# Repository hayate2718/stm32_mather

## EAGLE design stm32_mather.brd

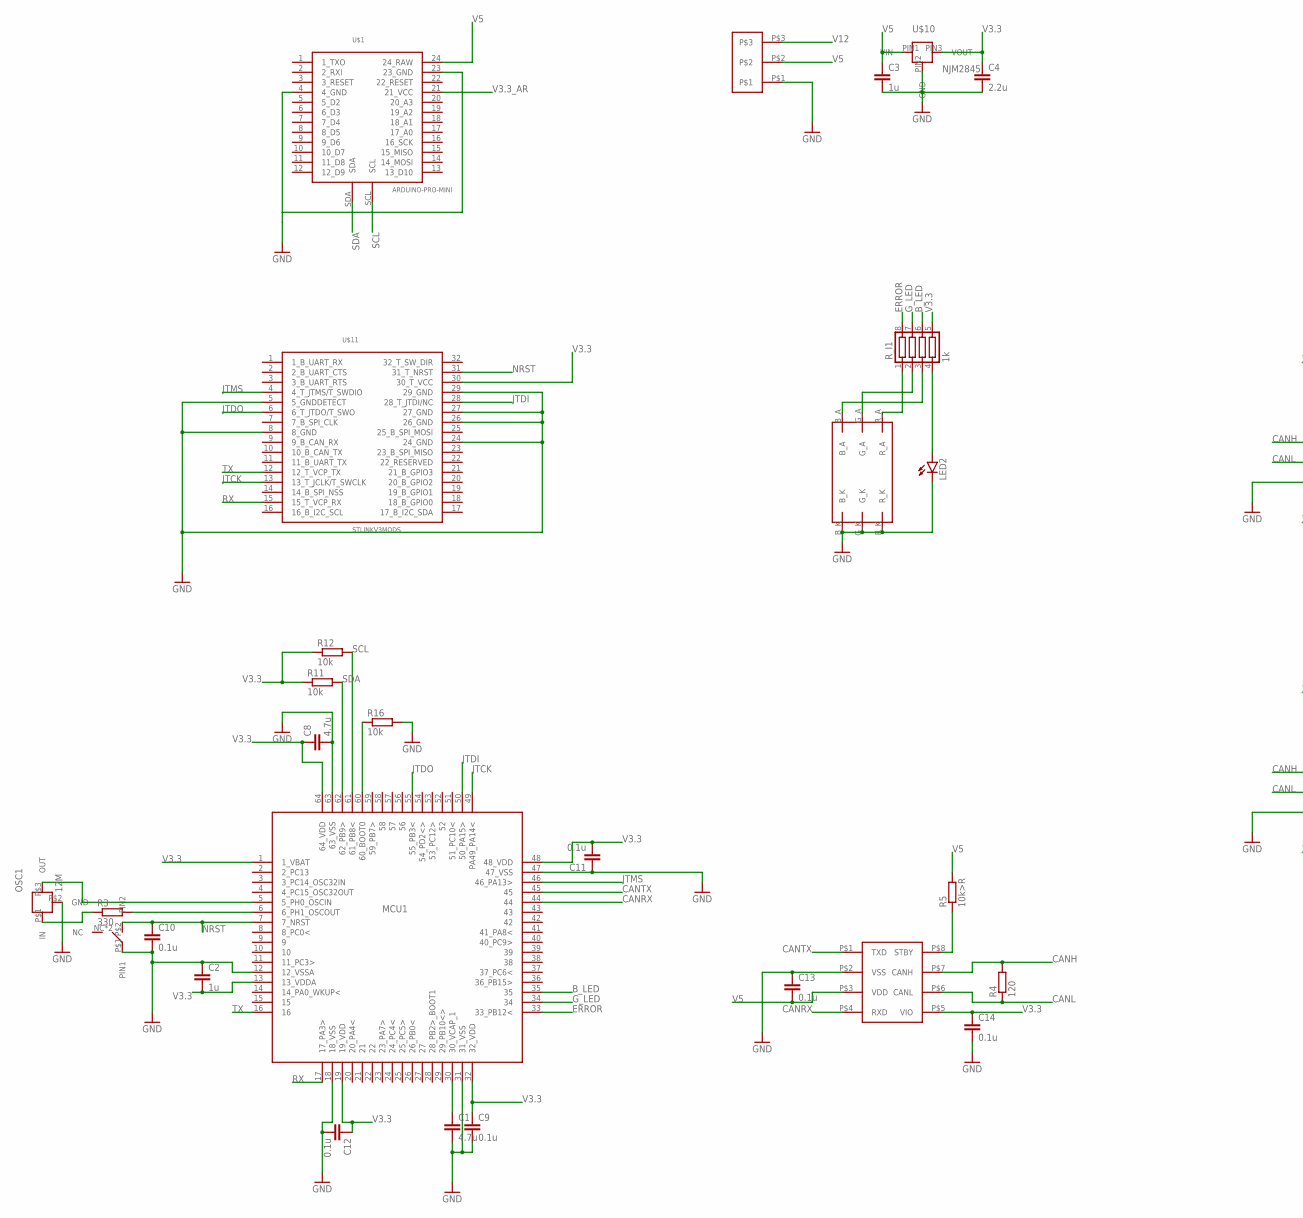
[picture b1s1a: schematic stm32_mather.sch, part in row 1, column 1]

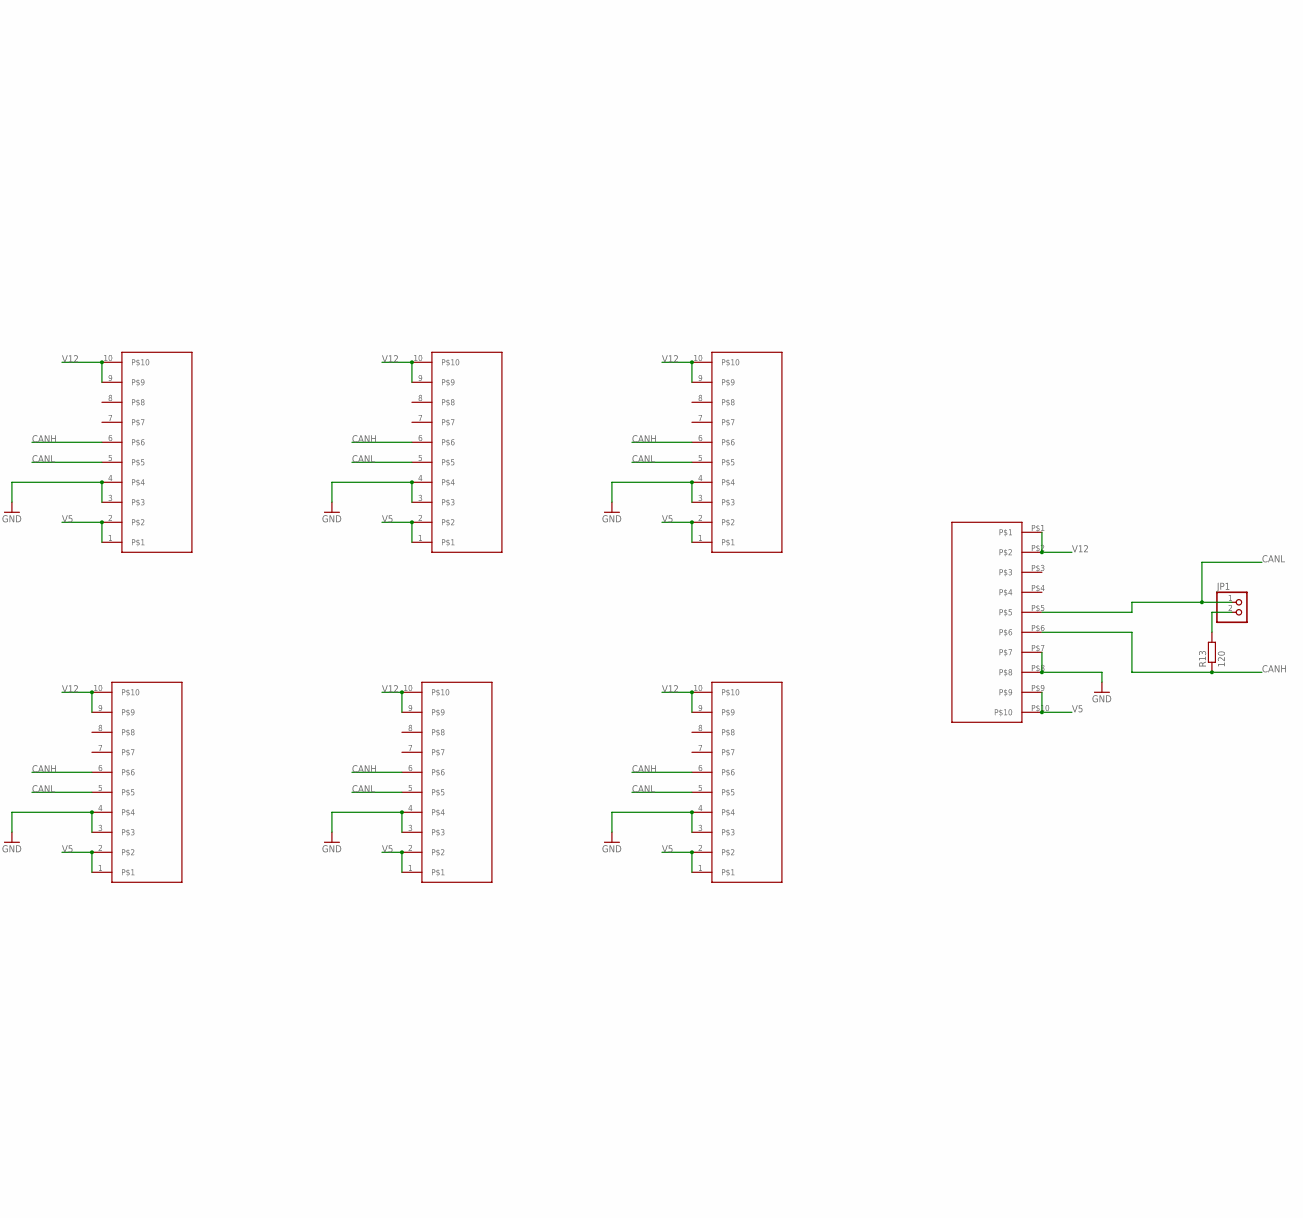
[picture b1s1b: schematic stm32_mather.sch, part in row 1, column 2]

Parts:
C1, C8: 4.7u; C1608
C2, C3: 1u; C1608
C4: 2.2u; C1608
C9, C10, C11, C12, C13, C14: 0.1u; C1608
JP1: PINHD-1X2; 1X02
LED2: 1608LED; 1608
MCU1: STM32F446; LQFP64-2
OSC1: 12M; CSTNE#
R3: 330; 1608
R4, R13: 120; 1608
R5: 10k>R; 1608
R11, R12, R16: 10k; 1608
R_I1: 1k; 0603X4RESISTOR
U$1: ARDUINO-PRO-MINI; ARDUINO_PRO_MINI
U$2, U$3, U$4, U$5, U$6, U$7: BOX10PBOX10PIN-MESU; BOX10P-MESU
U$8: BOX10PBOX10P-L; BOX10P-L
U$9: YUROBLOCK3
U$10: NJM2845; TO252
U$11: STLINKV3MODS
U$12: TAKUTOSUITTI2
U$13: MCP2562MCP2561-SN; SOIC8
U$15: RGB_LED

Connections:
B_LED: MCU1.35, R_I1.6
CANH: R4.2, R13.1, U$2.6, U$3.6, U$4.6, U$5.6, U$6.6, U$7.6, U$8.P$6, U$13.P$7 (CANH)
CANL: JP1.1, R4.1, U$2.5, U$3.5, U$4.5, U$5.5, U$6.5, U$7.5, U$8.P$5, U$13.P$6 (CANL)
CANRX: MCU1.44, U$13.P$4 (RXD)
CANTX: MCU1.45, U$13.P$1 (TXD)
ERROR: MCU1.33 (33_PB12<), R_I1.8
GND: C1.2, C2.1, C3.2, C4.2, C8.2, C9.2, C10.2, C11.1, C12.2, C13.1, C14.2, LED2.K, MCU1.12 (12_VSSA), MCU1.18 (18_VSS), MCU1.31 (31_VSS), MCU1.47 (47_VSS), MCU1.63 (63_VSS), OSC1.P$2 (GND), R16.2, U$1.4 (4_GND), U$1.23 (23_GND), U$2.3, U$2.4, U$3.3, U$3.4, U$4.3, U$4.4, U$5.3, U$5.4, U$6.3, U$6.4, U$7.3, U$7.4, U$8.P$7, U$8.P$8, U$9.P$1, U$10.PIN2 (GND), U$11.5 (5_GNDDETECT), U$11.8 (8_GND), U$11.24 (24_GND), U$11.26 (26_GND), U$11.27 (27_GND), U$11.29 (29_GND), U$12.P$1 (PIN1), U$13.P$2 (VSS), U$15.B_K, U$15.G_K, U$15.R_K
G_LED: MCU1.34, R_I1.7
JTCK: MCU1.49 (PA49_PA14<), U$11.13 (13_T_JCLK/T_SWCLK)
JTDI: MCU1.50 (50_PA15>), U$11.28 (28_T_JTDI/NC)
JTDO: MCU1.55 (55_PB3<), U$11.6 (6_T_JTDO/T_SWO)
JTMS: MCU1.46 (46_PA13>), U$11.4 (4_T_JTMS/T_SWDIO)
unnamed: C1.1, MCU1.30 (30_VCAP_1)
unnamed: OSC1.P$1 (IN), R3.1
unnamed: R_I1.1, U$15.R_A
unnamed: MCU1.5 (5_PH0_OSCIN), OSC1.P$3 (OUT)
unnamed: MCU1.6 (6_PH1_OSCOUT), R3.2
unnamed: R5.1, U$13.P$8 (STBY)
unnamed: JP1.2, R13.2
unnamed: R_I1.2, U$15.G_A
unnamed: R_I1.3, U$15.B_A
unnamed: LED2.A, R_I1.4
unnamed: MCU1.60 (60_BOOT0), R16.1
NRST: C10.1, MCU1.7 (7_NRST), U$11.31 (31_T_NRST), U$12.P$2 (PIN2)
RX: MCU1.17 (17_PA3>), U$11.15 (15_T_VCP_RX)
SCL: MCU1.61 (61_PB8<), R12.2, U$1.SCL
SDA: MCU1.62 (62_PB9>), R11.2, U$1.SDA
TX: MCU1.16, U$11.12 (12_T_VCP_TX)
V3.3: C2.2, C4.1, C8.1, C9.1, C11.2, C12.1, C14.1, MCU1.1 (1_VBAT), MCU1.13 (13_VDDA), MCU1.19 (19_VDD), MCU1.32 (32_VDD), MCU1.48 (48_VDD), MCU1.64 (64_VDD), R11.1, R12.1, R_I1.5, U$10.PIN3 (VOUT), U$11.30 (30_T_VCC), U$13.P$5 (VIO)
V3.3_AR: U$1.21 (21_VCC)
V5: C3.1, C13.2, R5.2, U$1.24 (24_RAW), U$2.1, U$2.2, U$3.1, U$3.2, U$4.1, U$4.2, U$5.1, U$5.2, U$6.1, U$6.2, U$7.1, U$7.2, U$8.P$9, U$8.P$10, U$9.P$2, U$10.PIN1 (VIN), U$13.P$3 (VDD)
V12: U$2.9, U$2.10, U$3.9, U$3.10, U$4.9, U$4.10, U$5.9, U$5.10, U$6.9, U$6.10, U$7.9, U$7.10, U$8.P$1, U$8.P$2, U$9.P$3

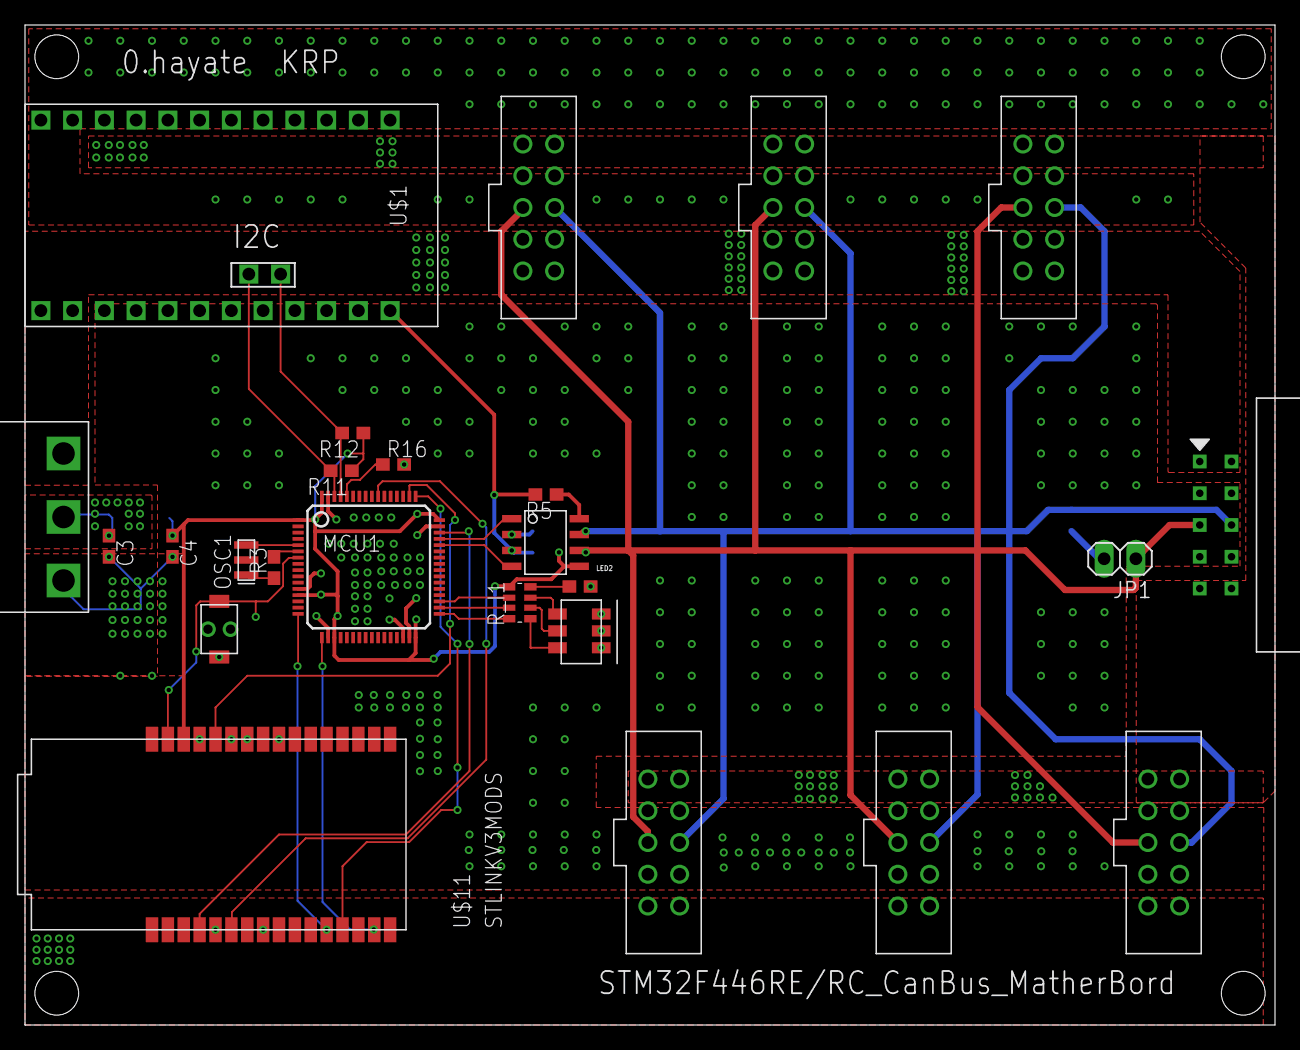
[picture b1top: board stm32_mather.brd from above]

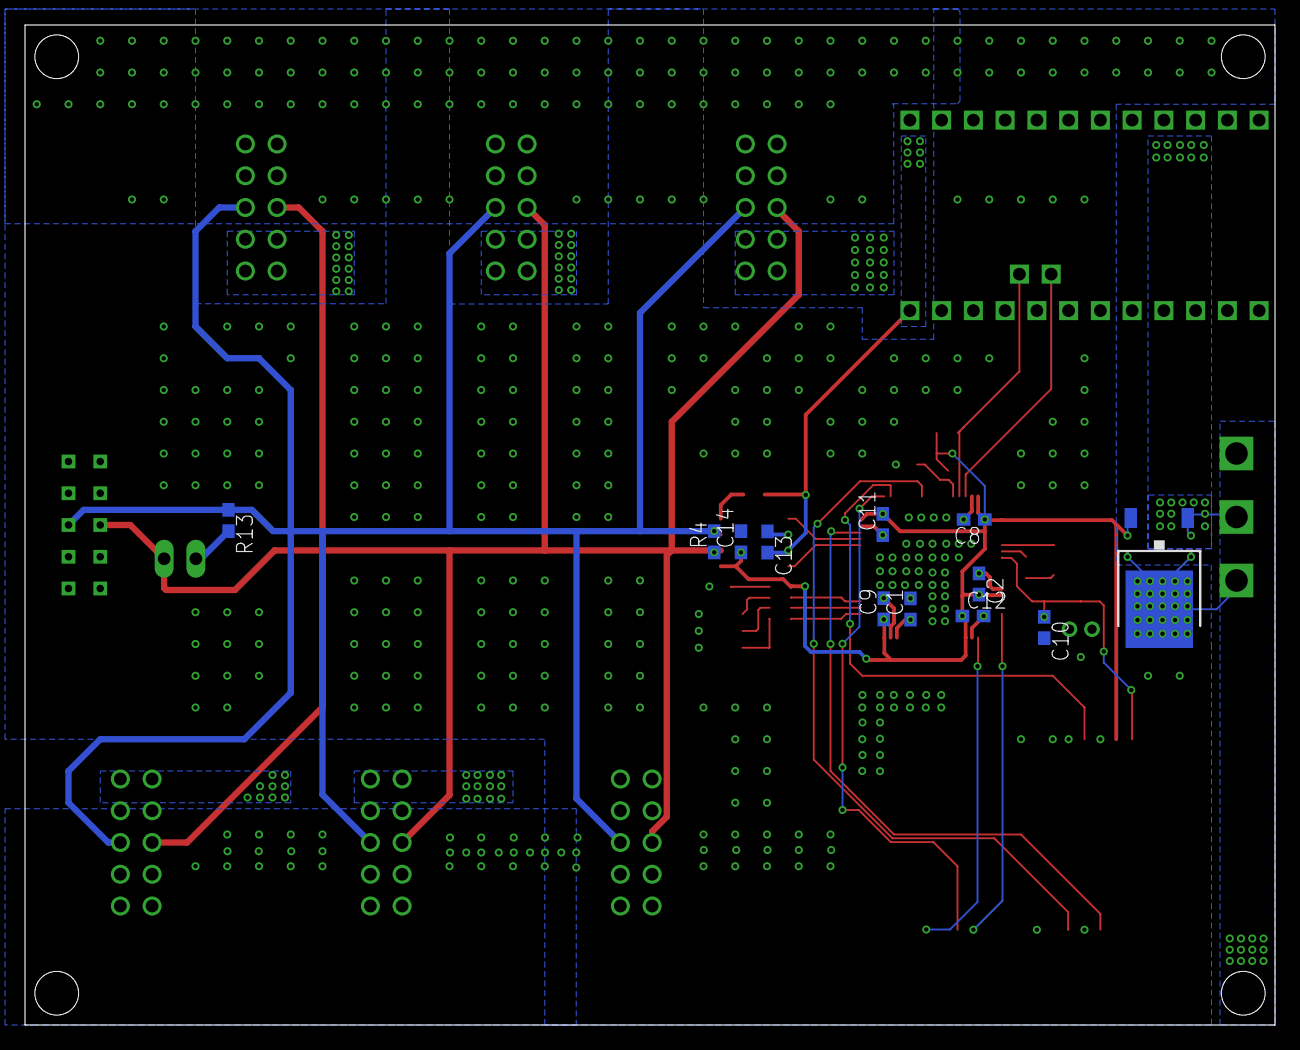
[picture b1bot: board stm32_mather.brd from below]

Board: 2 copper layers, 100.0 x 80.0 mm, 37 parts (12 on the bottom side), 31 nets.

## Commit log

2020-11-20 デバッガを組み込む方式に変更 3.3vのリニアレギュレータを単純化
2020-11-20 基板図の設計完了
2020-11-20 drcを通した
